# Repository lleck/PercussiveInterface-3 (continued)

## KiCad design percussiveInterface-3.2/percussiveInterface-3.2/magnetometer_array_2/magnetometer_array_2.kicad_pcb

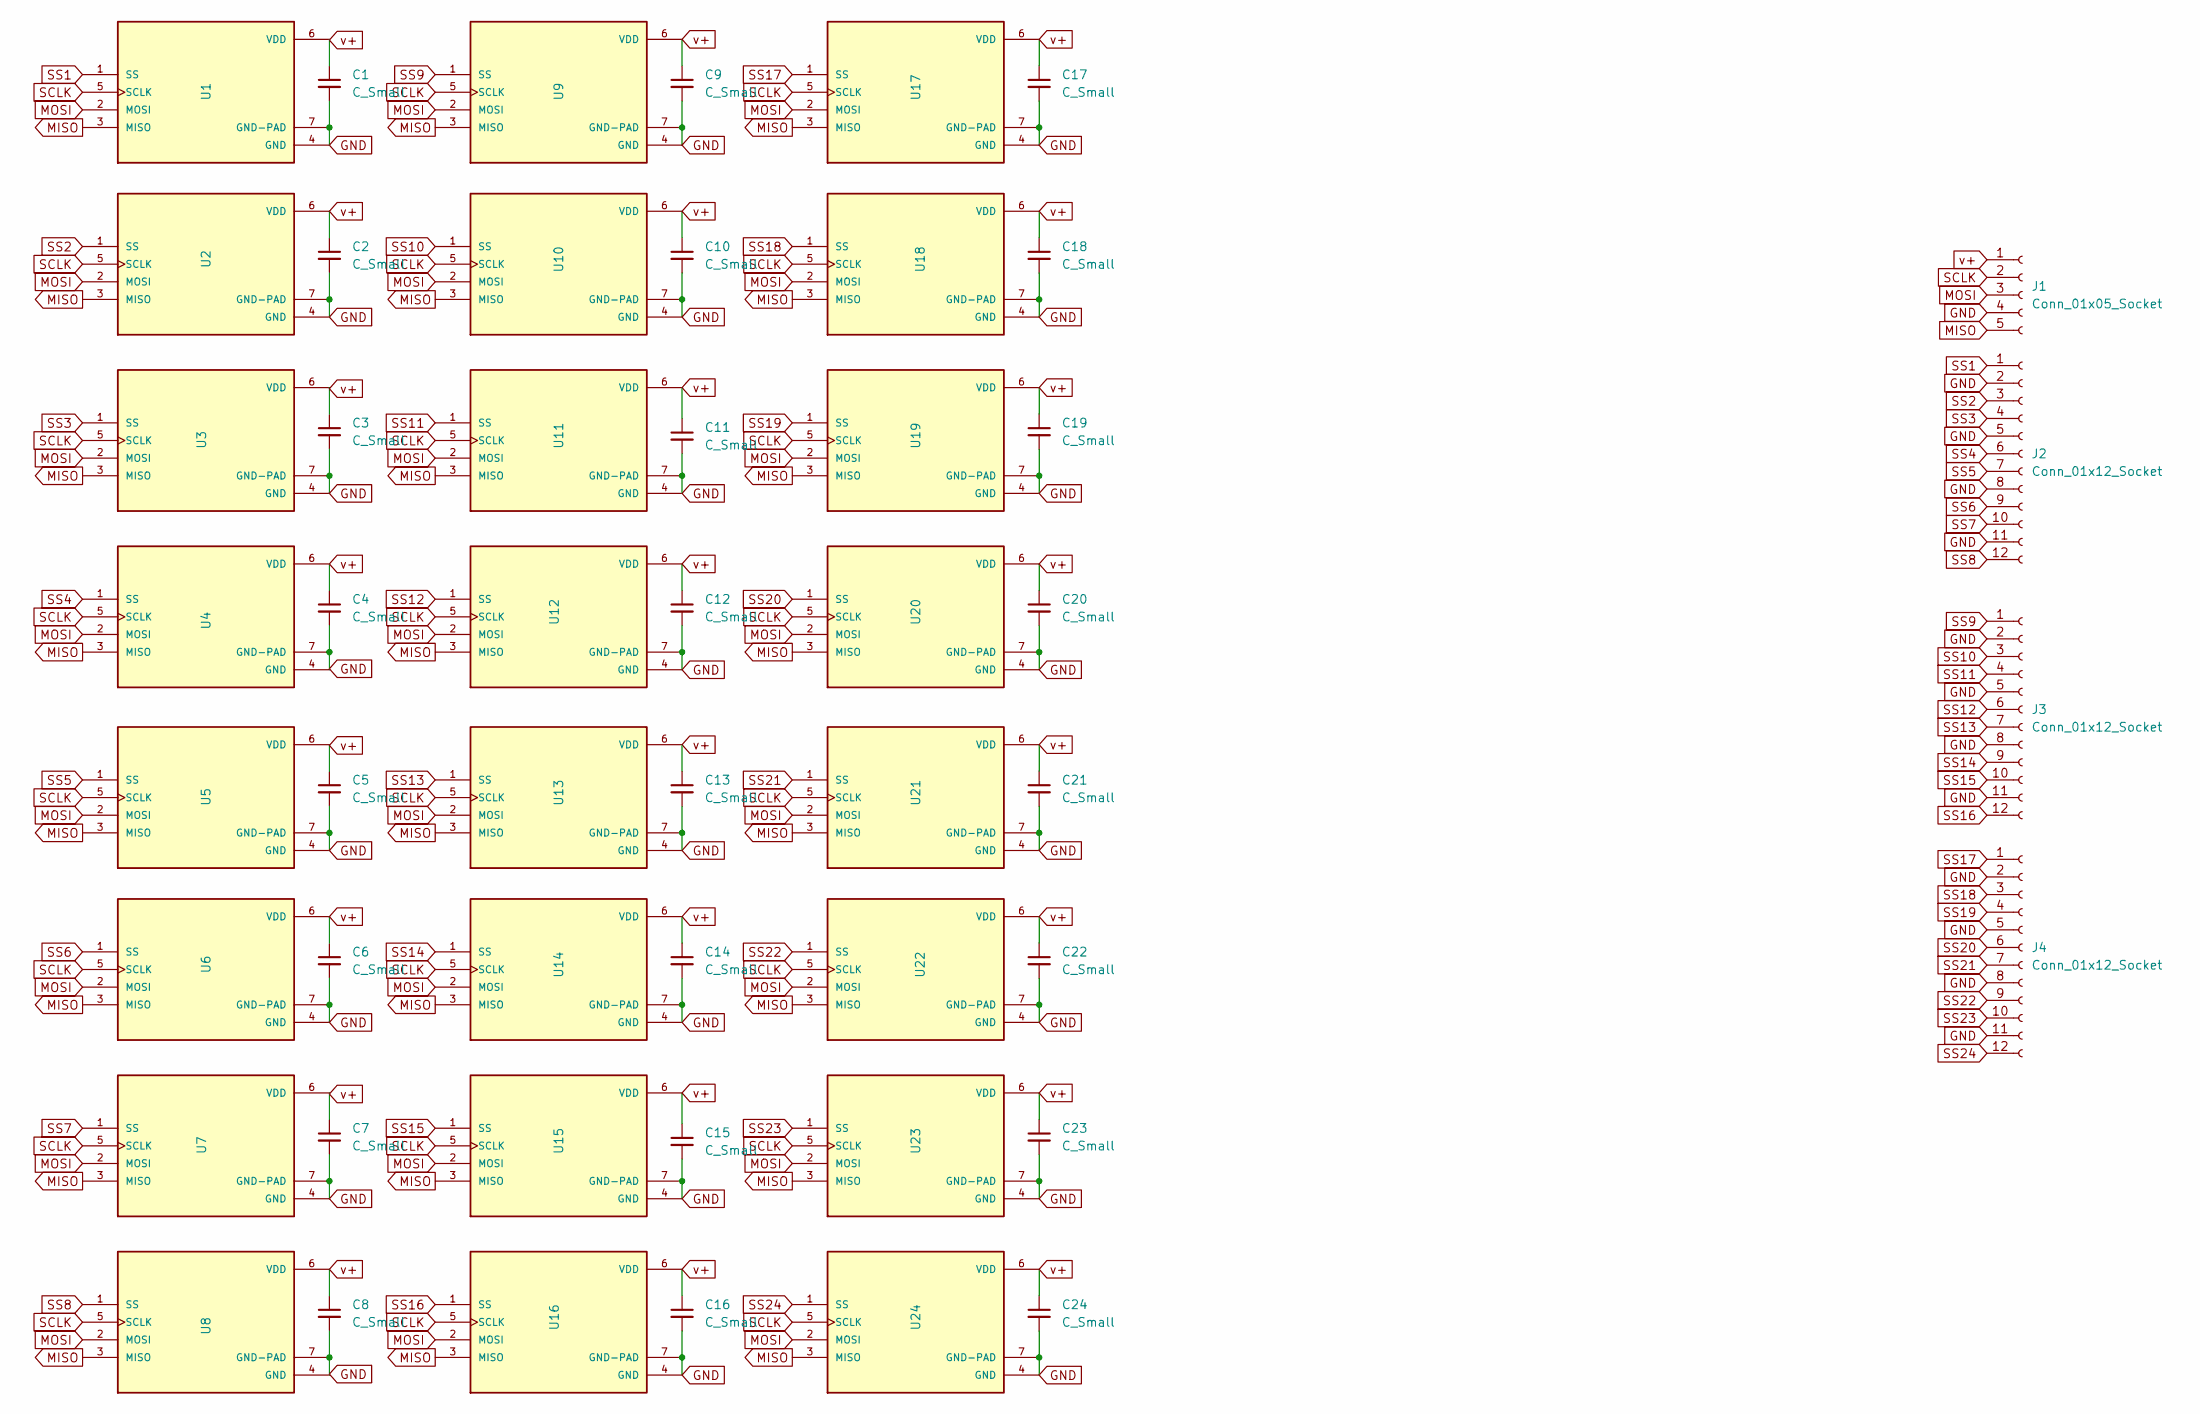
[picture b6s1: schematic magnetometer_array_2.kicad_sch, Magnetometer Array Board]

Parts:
C1, C2, C3, C4, C5, C6, C7, C8, C9, C10, C11, C12, C13, C14, C15, C16, C17, C18, C19, C20, C21, C22, C23, C24: C_Small; C_0201_0603Metric
J1: Conn_01x05_Socket; Harwin_M20-89005xx_1x05_P2.54mm_Horizontal
J2, J3, J4: Conn_01x12_Socket; Harwin_M20-89012xx_1x12_P2.54mm_Horizontal
U1, U2, U3, U4, U5, U6, U7, U8, U9, U10, U11, U12, U13, U14, U15, U16, U17, U18, U19, U20, U21, U22, U23, U24: SM225-10E; SON65P250X250X80-7N; PARTREV D

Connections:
GND: C1.2, C2.2, C3.2, C4.2, C5.2, C6.2, C7.2, C8.2, C9.2, C10.2, C11.2, C12.2, C13.2, C14.2, C15.2, C16.2, C17.2, C18.2, C19.2, C20.2, C21.2, C22.2, C23.2, C24.2, J1.4, J2.2, J2.5, J2.8, J2.11, J3.2, J3.5, J3.8, J3.11, J4.2, J4.5, J4.8, J4.11, U1.4 (GND), U1.7 (GND-PAD), U2.4 (GND), U2.7 (GND-PAD), U3.4 (GND), U3.7 (GND-PAD), U4.4 (GND), U4.7 (GND-PAD), U5.4 (GND), U5.7 (GND-PAD), U6.4 (GND), U6.7 (GND-PAD), U7.4 (GND), U7.7 (GND-PAD), U8.4 (GND), U8.7 (GND-PAD), U9.4 (GND), U9.7 (GND-PAD), U10.4 (GND), U10.7 (GND-PAD), U11.4 (GND), U11.7 (GND-PAD), U12.4 (GND), U12.7 (GND-PAD), U13.4 (GND), U13.7 (GND-PAD), U14.4 (GND), U14.7 (GND-PAD), U15.4 (GND), U15.7 (GND-PAD), U16.4 (GND), U16.7 (GND-PAD), U17.4 (GND), U17.7 (GND-PAD), U18.4 (GND), U18.7 (GND-PAD), U19.4 (GND), U19.7 (GND-PAD), U20.4 (GND), U20.7 (GND-PAD), U21.4 (GND), U21.7 (GND-PAD), U22.4 (GND), U22.7 (GND-PAD), U23.4 (GND), U23.7 (GND-PAD), U24.4 (GND), U24.7 (GND-PAD)
MISO: J1.5, U1.3 (MISO), U2.3 (MISO), U3.3 (MISO), U4.3 (MISO), U5.3 (MISO), U6.3 (MISO), U7.3 (MISO), U8.3 (MISO), U9.3 (MISO), U10.3 (MISO), U11.3 (MISO), U12.3 (MISO), U13.3 (MISO), U14.3 (MISO), U15.3 (MISO), U16.3 (MISO), U17.3 (MISO), U18.3 (MISO), U19.3 (MISO), U20.3 (MISO), U21.3 (MISO), U22.3 (MISO), U23.3 (MISO), U24.3 (MISO)
MOSI: J1.3, U1.2 (MOSI), U2.2 (MOSI), U3.2 (MOSI), U4.2 (MOSI), U5.2 (MOSI), U6.2 (MOSI), U7.2 (MOSI), U8.2 (MOSI), U9.2 (MOSI), U10.2 (MOSI), U11.2 (MOSI), U12.2 (MOSI), U13.2 (MOSI), U14.2 (MOSI), U15.2 (MOSI), U16.2 (MOSI), U17.2 (MOSI), U18.2 (MOSI), U19.2 (MOSI), U20.2 (MOSI), U21.2 (MOSI), U22.2 (MOSI), U23.2 (MOSI), U24.2 (MOSI)
SCLK: J1.2, U1.5 (SCLK), U2.5 (SCLK), U3.5 (SCLK), U4.5 (SCLK), U5.5 (SCLK), U6.5 (SCLK), U7.5 (SCLK), U8.5 (SCLK), U9.5 (SCLK), U10.5 (SCLK), U11.5 (SCLK), U12.5 (SCLK), U13.5 (SCLK), U14.5 (SCLK), U15.5 (SCLK), U16.5 (SCLK), U17.5 (SCLK), U18.5 (SCLK), U19.5 (SCLK), U20.5 (SCLK), U21.5 (SCLK), U22.5 (SCLK), U23.5 (SCLK), U24.5 (SCLK)
SS1: J2.1, U1.1 (SS)
SS2: J2.3, U2.1 (SS)
SS3: J2.4, U3.1 (SS)
SS4: J2.6, U4.1 (SS)
SS5: J2.7, U5.1 (SS)
SS6: J2.9, U6.1 (SS)
SS7: J2.10, U7.1 (SS)
SS8: J2.12, U8.1 (SS)
SS9: J3.1, U9.1 (SS)
SS10: J3.3, U10.1 (SS)
SS11: J3.4, U11.1 (SS)
SS12: J3.6, U12.1 (SS)
SS13: J3.7, U13.1 (SS)
SS14: J3.9, U14.1 (SS)
SS15: J3.10, U15.1 (SS)
SS16: J3.12, U16.1 (SS)
SS17: J4.1, U17.1 (SS)
SS18: J4.3, U18.1 (SS)
SS19: J4.4, U19.1 (SS)
SS20: J4.6, U20.1 (SS)
SS21: J4.7, U21.1 (SS)
SS22: J4.9, U22.1 (SS)
SS23: J4.10, U23.1 (SS)
SS24: J4.12, U24.1 (SS)
v+: C1.1, C2.1, C3.1, C4.1, C5.1, C6.1, C7.1, C8.1, C9.1, C10.1, C11.1, C12.1, C13.1, C14.1, C15.1, C16.1, C17.1, C18.1, C19.1, C20.1, C21.1, C22.1, C23.1, C24.1, J1.1, U1.6 (VDD), U2.6 (VDD), U3.6 (VDD), U4.6 (VDD), U5.6 (VDD), U6.6 (VDD), U7.6 (VDD), U8.6 (VDD), U9.6 (VDD), U10.6 (VDD), U11.6 (VDD), U12.6 (VDD), U13.6 (VDD), U14.6 (VDD), U15.6 (VDD), U16.6 (VDD), U17.6 (VDD), U18.6 (VDD), U19.6 (VDD), U20.6 (VDD), U21.6 (VDD), U22.6 (VDD), U23.6 (VDD), U24.6 (VDD)

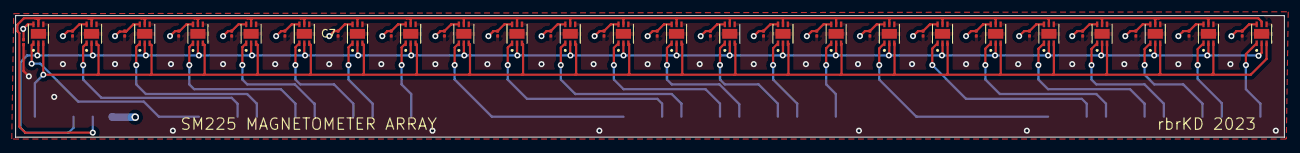
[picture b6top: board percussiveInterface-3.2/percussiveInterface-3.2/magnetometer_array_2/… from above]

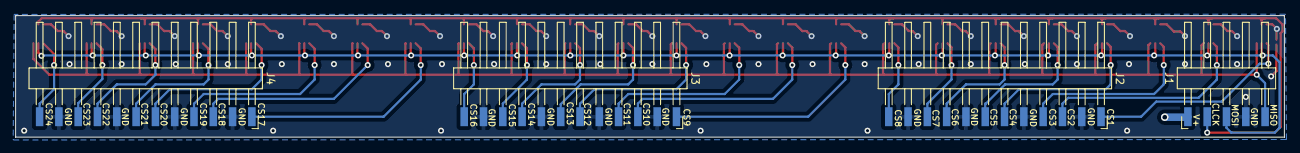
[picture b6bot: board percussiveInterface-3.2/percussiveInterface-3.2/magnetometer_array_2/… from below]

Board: 4 copper layers, 167.0 x 16.0 mm, 52 parts (4 on the bottom side), 29 nets.

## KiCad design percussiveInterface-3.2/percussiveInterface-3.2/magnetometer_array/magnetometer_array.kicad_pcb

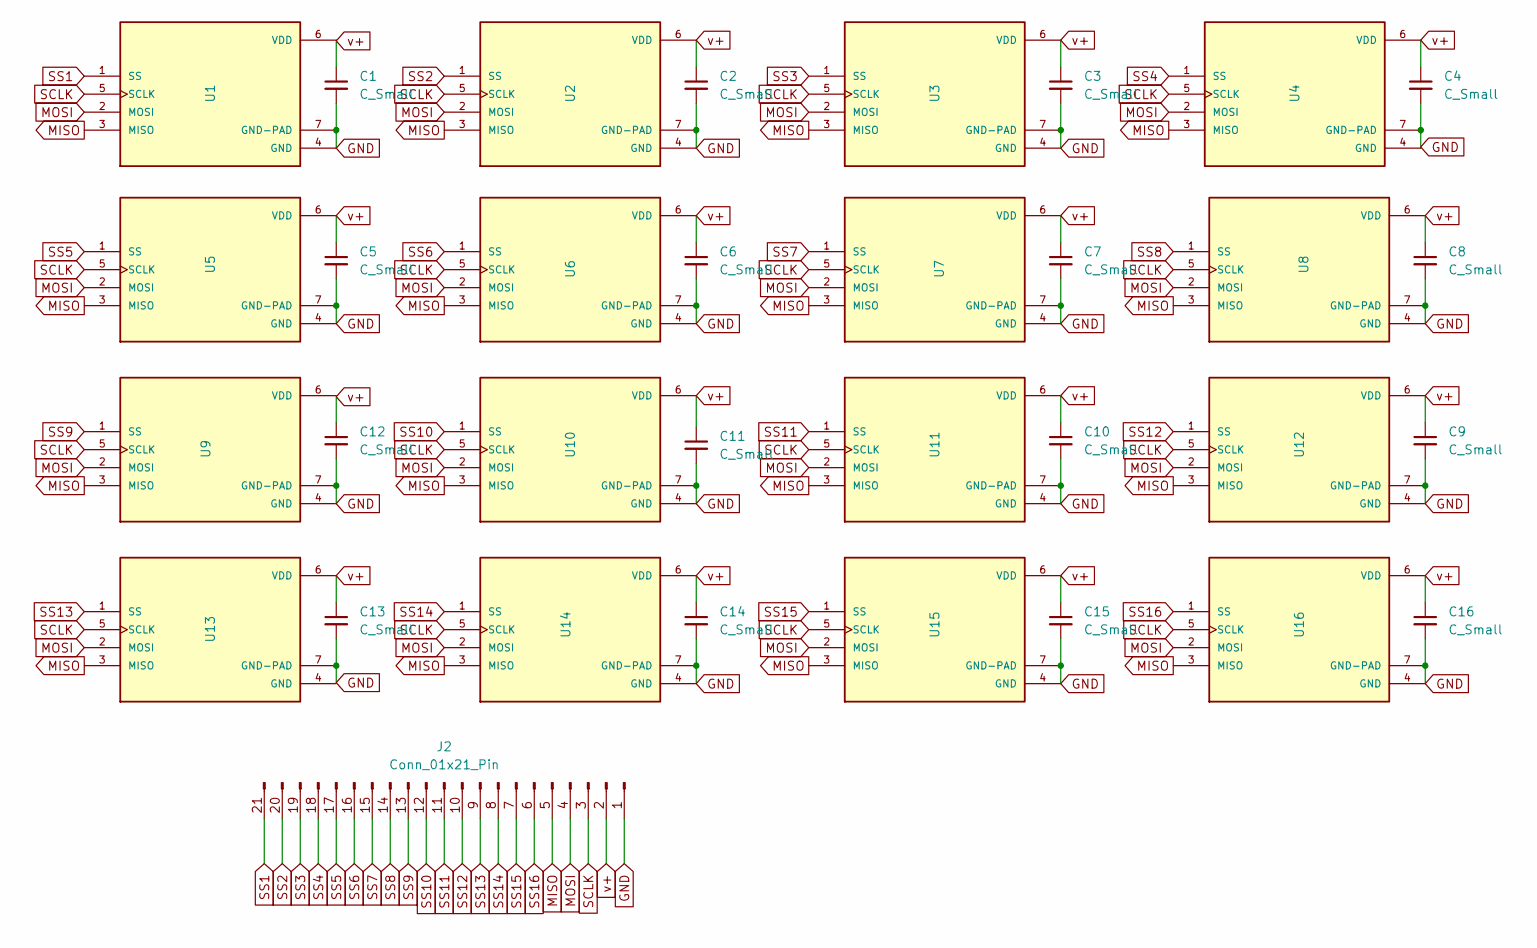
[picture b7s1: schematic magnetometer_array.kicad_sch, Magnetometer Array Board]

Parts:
C1, C2, C3, C4, C5, C6, C7, C8, C9, C10, C11, C12, C13, C14, C15, C16: C_Small; C_0201_0603Metric
J2: Conn_01x21_Pin; PinHeader_1x21_P2.54mm_Horizontal
U1, U2, U3, U4, U5, U6, U7, U8, U9, U10, U11, U12, U13, U14, U15, U16: SM225-10E; NVE SM225 10E; PARTREV D

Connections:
GND: C1.2, C2.2, C3.2, C4.2, C5.2, C6.2, C7.2, C8.2, C9.2, C10.2, C11.2, C12.2, C13.2, C14.2, C15.2, C16.2, J2.1, U1.4 (GND), U1.7 (GND-PAD), U2.4 (GND), U2.7 (GND-PAD), U3.4 (GND), U3.7 (GND-PAD), U4.4 (GND), U4.7 (GND-PAD), U5.4 (GND), U5.7 (GND-PAD), U6.4 (GND), U6.7 (GND-PAD), U7.4 (GND), U7.7 (GND-PAD), U8.4 (GND), U8.7 (GND-PAD), U9.4 (GND), U9.7 (GND-PAD), U10.4 (GND), U10.7 (GND-PAD), U11.4 (GND), U11.7 (GND-PAD), U12.4 (GND), U12.7 (GND-PAD), U13.4 (GND), U13.7 (GND-PAD), U14.4 (GND), U14.7 (GND-PAD), U15.4 (GND), U15.7 (GND-PAD), U16.4 (GND), U16.7 (GND-PAD)
MISO: J2.5, U1.3 (MISO), U2.3 (MISO), U3.3 (MISO), U4.3 (MISO), U5.3 (MISO), U6.3 (MISO), U7.3 (MISO), U8.3 (MISO), U9.3 (MISO), U10.3 (MISO), U11.3 (MISO), U12.3 (MISO), U13.3 (MISO), U14.3 (MISO), U15.3 (MISO), U16.3 (MISO)
MOSI: J2.4, U1.2 (MOSI), U2.2 (MOSI), U3.2 (MOSI), U4.2 (MOSI), U5.2 (MOSI), U6.2 (MOSI), U7.2 (MOSI), U8.2 (MOSI), U9.2 (MOSI), U10.2 (MOSI), U11.2 (MOSI), U12.2 (MOSI), U13.2 (MOSI), U14.2 (MOSI), U15.2 (MOSI), U16.2 (MOSI)
SCLK: J2.3, U1.5 (SCLK), U2.5 (SCLK), U3.5 (SCLK), U4.5 (SCLK), U5.5 (SCLK), U6.5 (SCLK), U7.5 (SCLK), U8.5 (SCLK), U9.5 (SCLK), U10.5 (SCLK), U11.5 (SCLK), U12.5 (SCLK), U13.5 (SCLK), U14.5 (SCLK), U15.5 (SCLK), U16.5 (SCLK)
SS1: J2.21, U1.1 (SS)
SS2: J2.20, U2.1 (SS)
SS3: J2.19, U3.1 (SS)
SS4: J2.18, U4.1 (SS)
SS5: J2.17, U5.1 (SS)
SS6: J2.16, U6.1 (SS)
SS7: J2.15, U7.1 (SS)
SS8: J2.14, U8.1 (SS)
SS9: J2.13, U9.1 (SS)
SS10: J2.12, U10.1 (SS)
SS11: J2.11, U11.1 (SS)
SS12: J2.10, U12.1 (SS)
SS13: J2.9, U13.1 (SS)
SS14: J2.8, U14.1 (SS)
SS15: J2.7, U15.1 (SS)
SS16: J2.6, U16.1 (SS)
v+: C1.1, C2.1, C3.1, C4.1, C5.1, C6.1, C7.1, C8.1, C9.1, C10.1, C11.1, C12.1, C13.1, C14.1, C15.1, C16.1, J2.2, U1.6 (VDD), U2.6 (VDD), U3.6 (VDD), U4.6 (VDD), U5.6 (VDD), U6.6 (VDD), U7.6 (VDD), U8.6 (VDD), U9.6 (VDD), U10.6 (VDD), U11.6 (VDD), U12.6 (VDD), U13.6 (VDD), U14.6 (VDD), U15.6 (VDD), U16.6 (VDD)

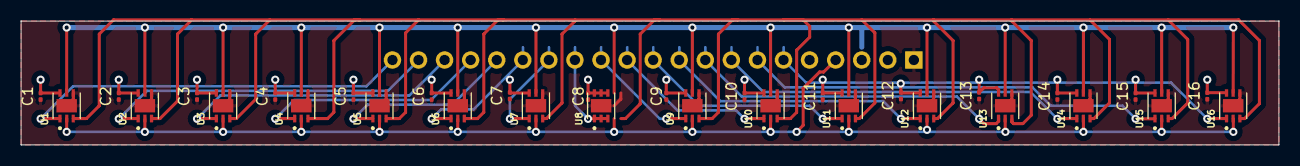
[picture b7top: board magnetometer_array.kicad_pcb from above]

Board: 4 copper layers, 122.6 x 12.1 mm, 33 parts (1 on the bottom side), 21 nets.

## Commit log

2023-05-05 lleck
    first commit
2023-05-05 deleted
2023-05-05 rename3
2023-05-05 renaminggg
2023-05-09 conversion to 4layer
    inner ground and power layer and seperate outer layers for analog and
    digital signal routing
2023-05-09 folder structure
2023-05-09 small changes
2023-05-25 analog read 3 hall sens Arduino Code 1st
2023-05-27 notes
2023-05-29 more notes
2023-06-08 processing sketch
2023-06-14 backups
2023-06-19 processing
2023-06-29 differential reading of hall sensors
2023-06-30 dsfvadfv
2023-07-15 new layout 3.2
2023-07-15 layout 3.2
2023-07-15 nochmal update
2023-08-31 magnetometer array
2023-08-31 magnetometer arra<
2023-08-31 slightl<y new
2023-08-31 sdzhjrtghj
2023-09-20 stuff
2023-09-28 coil plugin etc
2023-10-08 new magnetoarray
2023-10-30 new arrray
2023-10-31 plentay stuffx
2023-11-03 many changes
2023-11-06 quadrillion changes
2023-11-09 almost there but not
2023-11-13 homework again
2023-11-14 almost ahgsngarsn
2023-11-15 jlc board
2023-11-15 jlc board ...
2023-11-16 bremen_workation
2023-11-19 full integrated with ti magnetometer
2023-11-21 afaeaefdga
2023-11-21 asgfebgsdfbas
2023-11-22 xgfbdbg
2023-11-23 yoyoyoyoy
2023-12-01 fgvjbhkljdtzrj
2023-12-05 before production / pinout ESP IO
2023-12-05 dfzvgh
2023-12-14 Code slowly layed out
2023-12-14 bla bla
2023-12-20 position readings
2023-12-20 chngs
2023-12-20 fastTrig und so
2023-12-22 trigger algo
2023-12-27 this & that
2023-12-28 bliblablub
2023-12-28 sevgfcs
2023-12-30 trblz
2023-12-30 rfrnz
2023-12-30 cghfjkvghf
2023-12-30 cdfvgh
2023-12-30 dfggsdfg
2024-01-04 456789
2024-01-04 5678654
2024-01-04 243636
2024-01-04 45735673456
2024-01-04 12341234
2024-01-07 sdfgdafg
2024-01-10 Logic Analyzer test SPI
2024-01-12 finaly reading all the sensors (uff)
2024-01-14 derfgsrtghsr
2024-02-03 240203 status quo
2024-02-03 restored from 01.02
2024-02-03 adfsghrewaet
2024-02-03 wrzetrte
2024-02-03 weghsdrfghsfgh
2024-02-03 wghsdrtghsrtg
2024-02-03 23452354
2024-02-03 346245673456
2024-02-03 240203_sechsuhr
2024-02-03 adfgadfg
2024-02-03 12341346345621345
2024-02-03 back to a working state
2024-02-04 fastled
2024-02-20 first 20.02.24
2024-02-20 readPosition(old)
2024-02-22 preKolloquium Commit
